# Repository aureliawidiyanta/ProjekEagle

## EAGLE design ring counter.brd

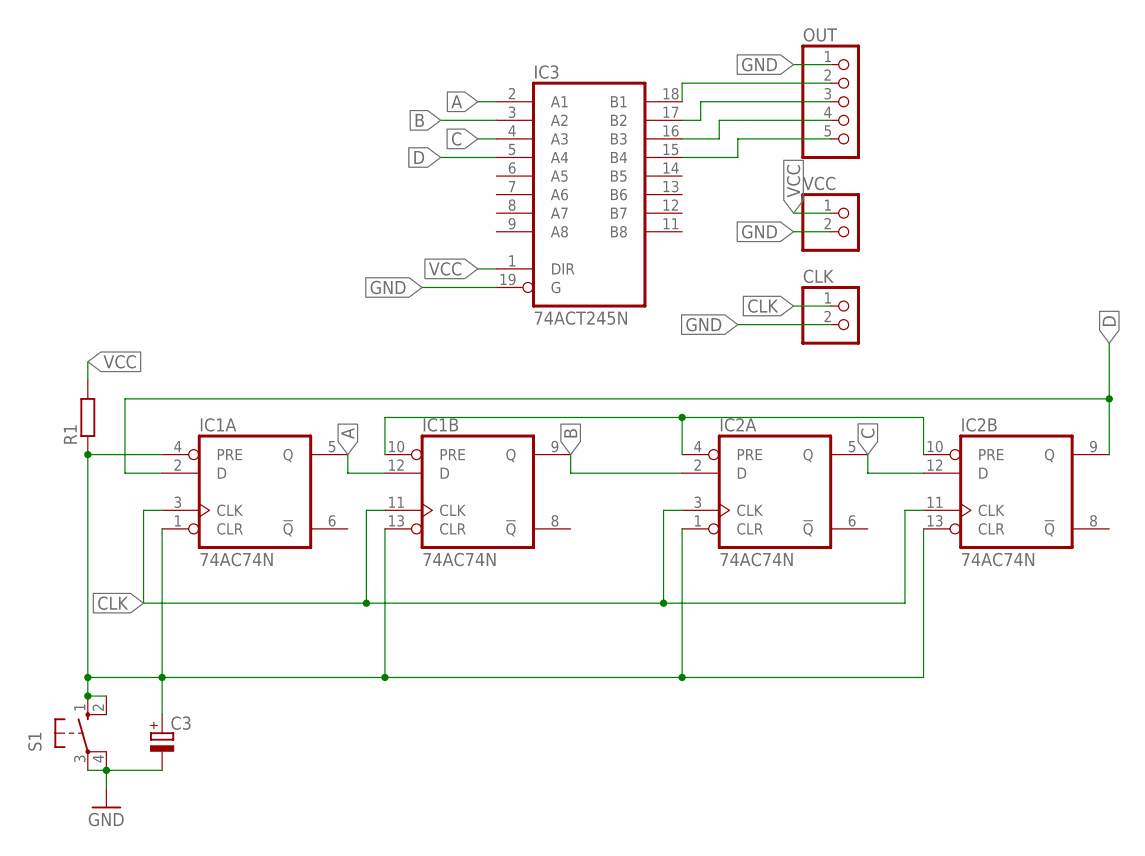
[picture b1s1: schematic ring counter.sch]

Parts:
C3: CPOL-EUE2,5-6E; E2,5-6E
CLK: PINHD-1X2; 1X02
IC1, IC2: 74AC74N; DIL14
IC3: 74ACT245N; DIL20
OUT: PINHD-1X5; 1X05
R1: R-EU_0207/12; 0207/12
S1: 10-XX; B3F-10XX
VCC: PINHD-1X2; 1X02

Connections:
A: IC1.5 (Q), IC1.12 (D), IC3.2 (A1)
B: IC1.9 (Q), IC2.2 (D), IC3.3 (A2)
C: IC2.5 (Q), IC2.12 (D), IC3.4 (A3)
CLK: CLK.1, IC1.3 (CLK), IC1.11 (CLK), IC2.3 (CLK), IC2.11 (CLK)
D: IC1.2 (D), IC2.9 (Q), IC3.5 (A4)
GND: C3.-, CLK.2, IC1.7 (GND), IC2.7 (GND), IC3.10 (GND), IC3.19 (G), OUT.1, S1.3, S1.4 (P1), VCC.2
unnamed: IC1.10 (PRE), IC2.4 (PRE), IC2.10 (PRE)
unnamed: C3.+, IC1.1 (CLR), IC1.4 (PRE), IC1.13 (CLR), IC2.1 (CLR), IC2.13 (CLR), R1.1, S1.1 (S), S1.2 (S1)
unnamed: IC3.18 (B1), OUT.2
unnamed: IC3.17 (B2), OUT.3
unnamed: IC3.16 (B3), OUT.4
unnamed: IC3.15 (B4), OUT.5
VCC: IC1.14 (VCC), IC2.14 (VCC), IC3.1 (DIR), IC3.20 (VCC), R1.2, VCC.1

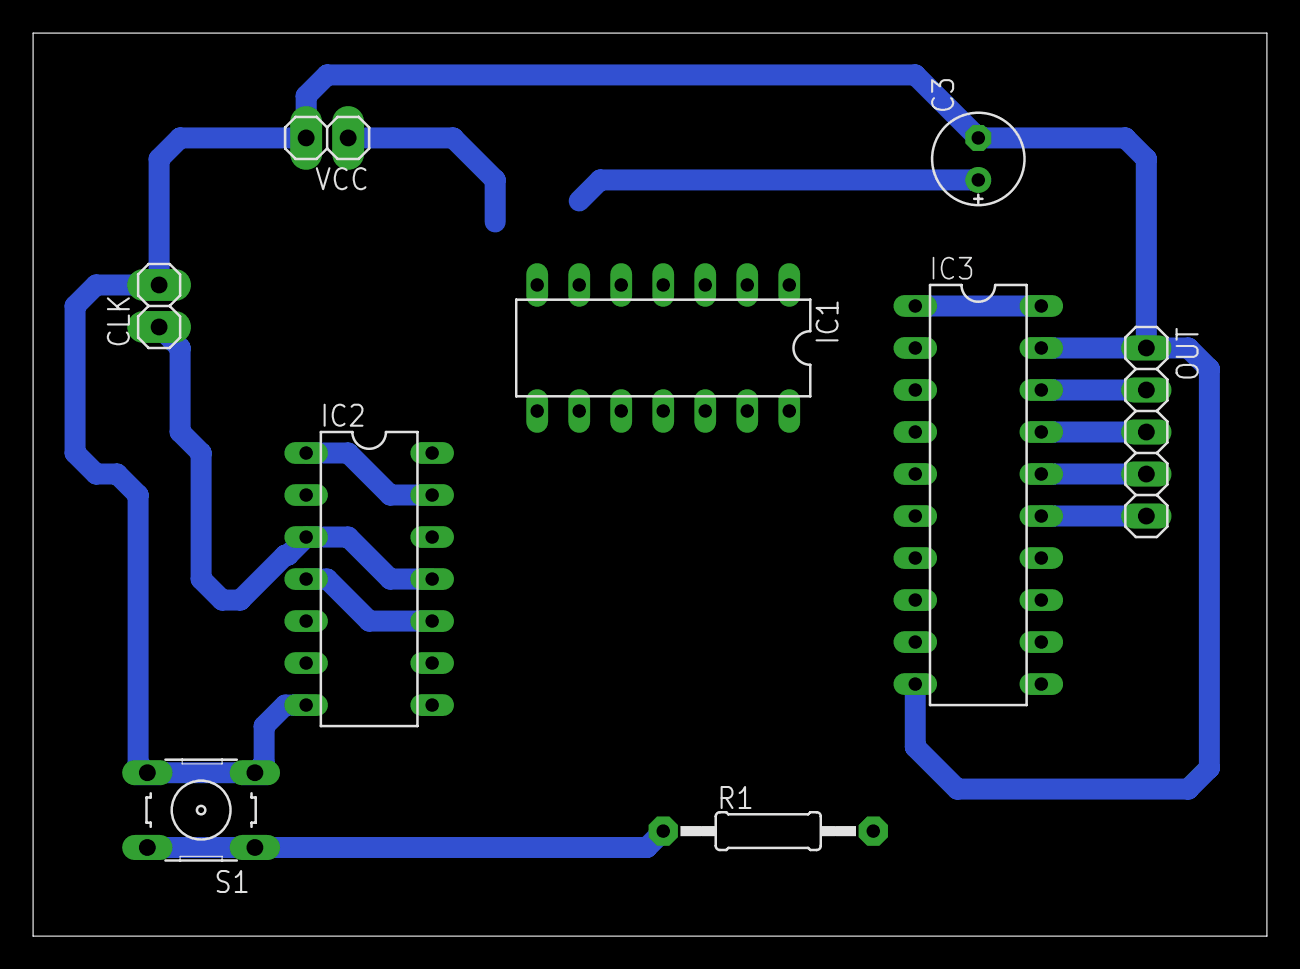
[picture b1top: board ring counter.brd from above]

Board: 2 copper layers, 74.6 x 54.6 mm, 9 parts (0 on the bottom side), 13 nets.

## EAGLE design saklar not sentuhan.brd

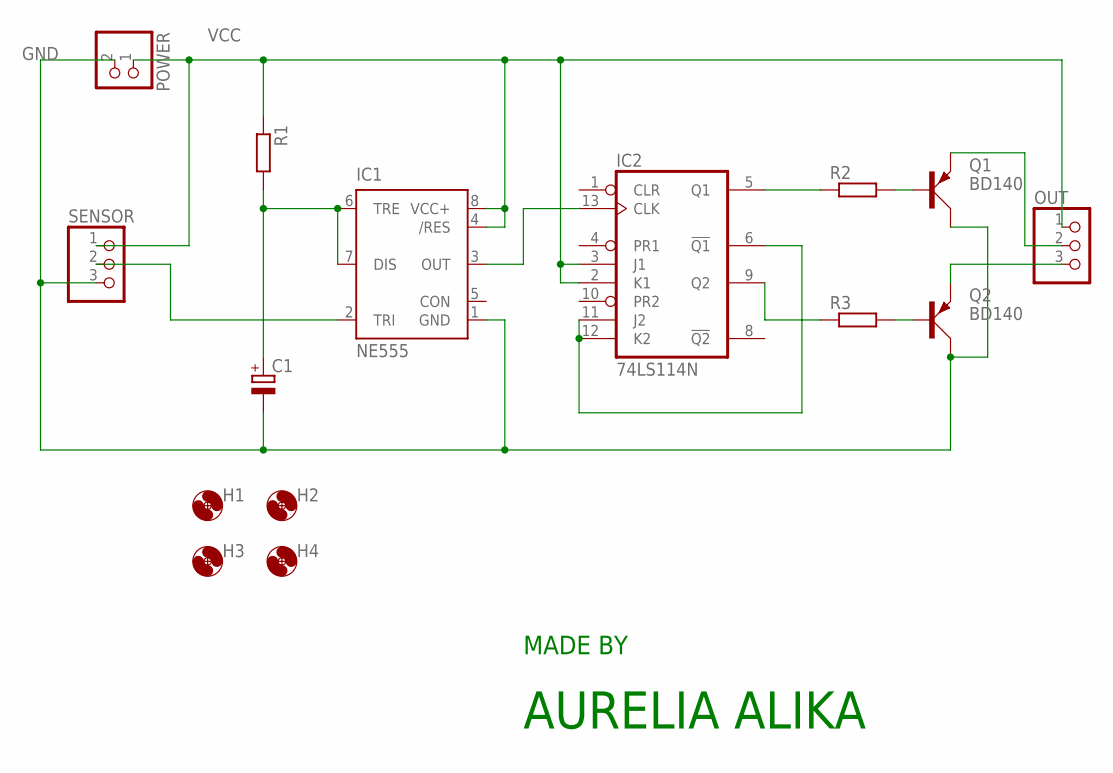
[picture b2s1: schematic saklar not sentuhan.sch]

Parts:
C1: CPOL-EUE2,5-6E; E2,5-6E
H1, H2, H3, H4: MOUNT-HOLE3.6; 3,6
IC1: NE555; DIL-08
IC2: 74LS114N; DIL14
OUT: PINHD-1X3; 1X03
POWER: PINHD-1X2; 1X02
Q1, Q2: BD140; TO126AV
R1, R2, R3: R-EU_0207/15; 0207/15
SENSOR: PINHD-1X3; 1X03

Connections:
GND: C1.-, IC1.1 (GND), IC2.7 (GND), POWER.2, Q1.C, Q2.C, SENSOR.3
unnamed: IC1.3 (OUT), IC2.13 (CLK)
unnamed: OUT.2, Q1.E
unnamed: IC2.5 (Q1), R2.1
unnamed: OUT.3, Q2.E
unnamed: C1.+, IC1.6 (TRE), IC1.7 (DIS), R1.2
unnamed: IC1.2 (TRI), SENSOR.2
unnamed: Q1.B, R2.2
unnamed: IC2.9 (Q2), R3.1
unnamed: Q2.B, R3.2
unnamed: IC2.6 (!Q1), IC2.11 (J2), IC2.12 (K2)
VCC: IC1.4 (/RES), IC1.8 (VCC+), IC2.2 (K1), IC2.3 (J1), IC2.14 (VCC), OUT.1, POWER.1, R1.1, SENSOR.1

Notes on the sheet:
MADE BY
AURELIA ALIKA

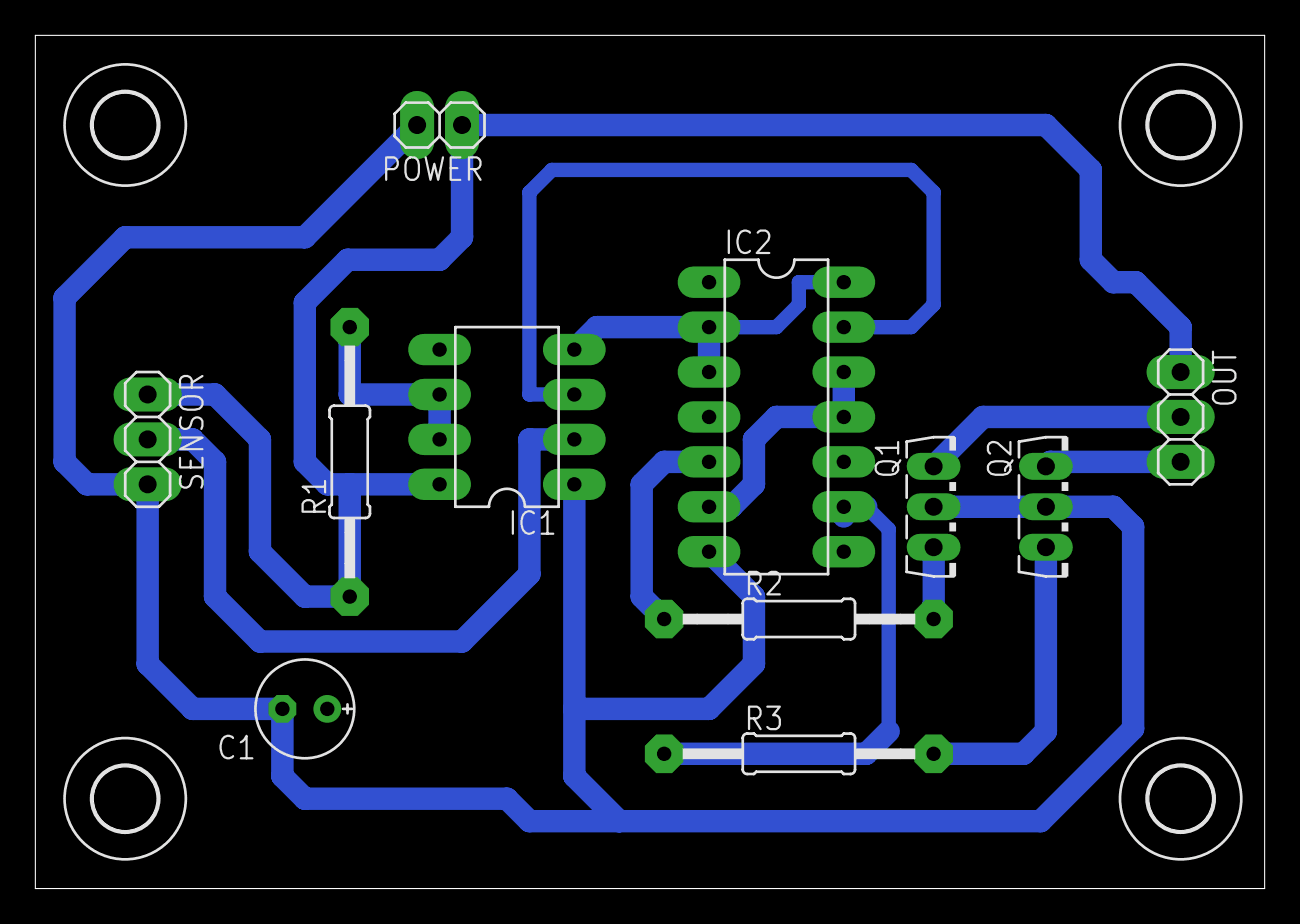
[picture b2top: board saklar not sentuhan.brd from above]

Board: 2 copper layers, 69.5 x 48.2 mm, 15 parts (0 on the bottom side), 12 nets.

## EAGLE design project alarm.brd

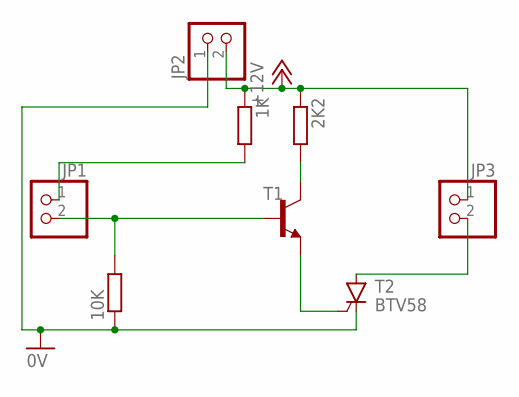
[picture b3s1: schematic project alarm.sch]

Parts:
1K, 2K2, 10K: R-EU_0207/15; 0207/15
JP1, JP2, JP3: PINHD-1X2; 1X02
T1: BC107A-NPN-TO18-EBC; TO18
T2: BTV58; TO220CS

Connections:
0V: 10K.1, JP2.1, T2.C
+12V: 1K.1, 2K2.1, JP2.2, JP3.1
unnamed: 10K.2, JP1.2, T1.2 (B)
unnamed: 2K2.2, T1.3 (C)
unnamed: 1K.2, JP1.1
unnamed: T1.1 (E), T2.G
unnamed: JP3.2, T2.A

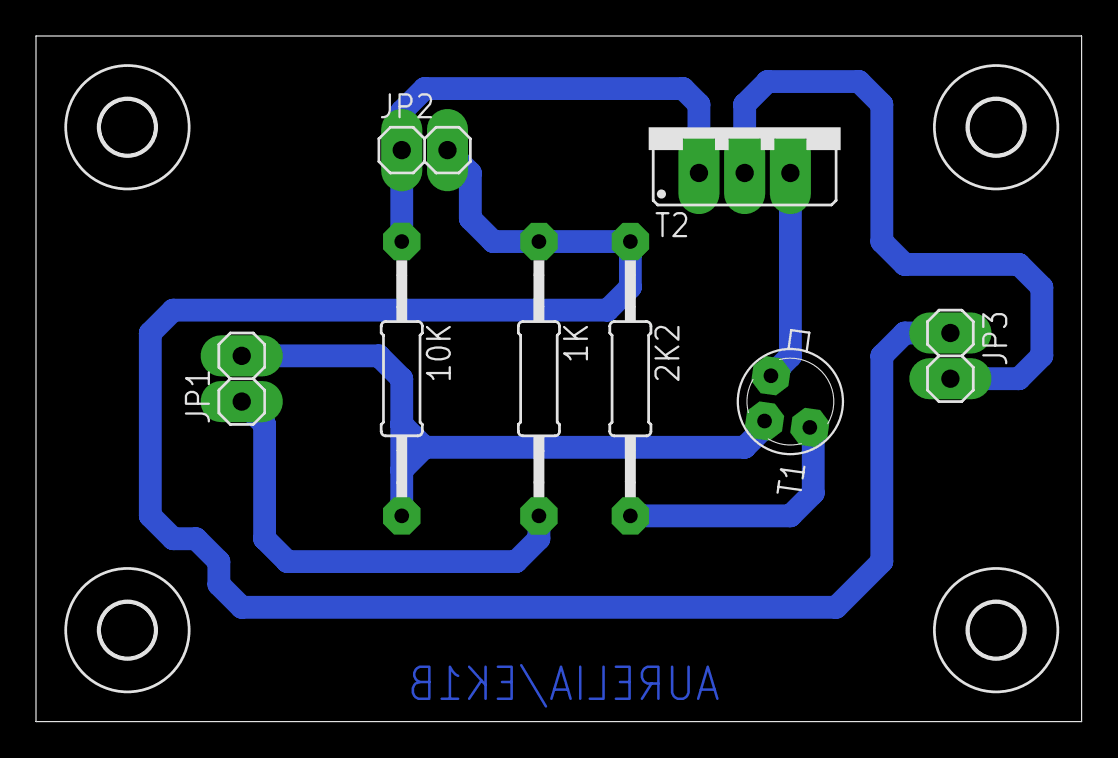
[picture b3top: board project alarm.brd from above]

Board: 2 copper layers, 58.1 x 38.1 mm, 12 parts (0 on the bottom side), 7 nets.

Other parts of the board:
U$1, U$2, U$3, U$4: 3,0

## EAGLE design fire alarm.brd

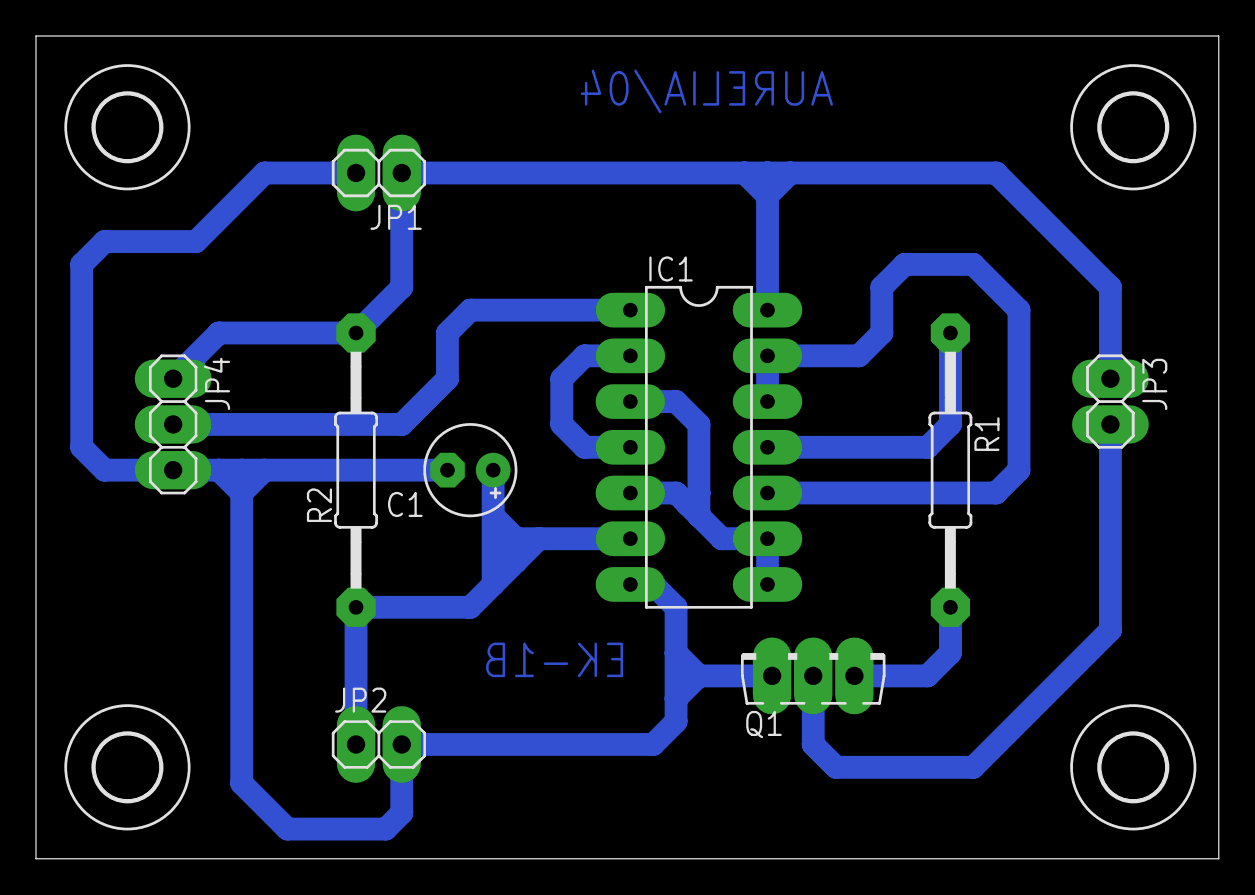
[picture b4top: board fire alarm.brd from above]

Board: 2 copper layers, 65.7 x 45.7 mm, 13 parts (0 on the bottom side), 10 nets.

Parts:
C1: E2,5-5
H1, H2, H3, H4: MOUNT-HOLE3.6; 3,6
IC1: 4093N; DIL14
JP1, JP2, JP3: 1X02
JP4: 1X03
Q1: BD139; TO126AV
R1, R2: 0207/15

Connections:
unnamed: IC1.11, R1.1
unnamed: IC1.2, IC1.4
unnamed: IC1.3, IC1.5, IC1.8, IC1.9
unnamed: Q1.B, R1.2
unnamed: IC1.10, IC1.12, IC1.13
unnamed: C1.+, IC1.6, JP2.1, R2.1
unnamed: IC1.1, JP4.2
unnamed: JP3.2, Q1.C
VDD: IC1.14, JP1.1, JP3.1, JP4.1, R2.2
VSS: C1.-, IC1.7, JP1.2, JP2.2, JP4.3, Q1.E

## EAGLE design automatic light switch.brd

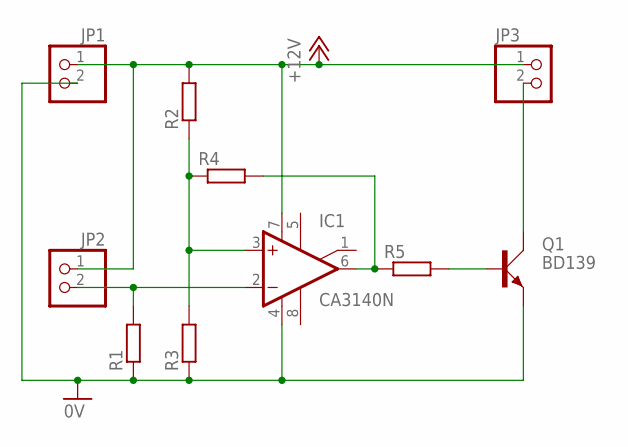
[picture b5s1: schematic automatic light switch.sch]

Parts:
IC1: CA3140N; DIL08
JP1, JP2, JP3: PINHD-1X2; 1X02
Q1: BD139; TO126AV
R1, R2, R3, R4, R5: R-EU_0207/15; 0207/15

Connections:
0V: IC1.4 (V-), JP1.2, Q1.E, R1.1, R3.1
+12V: IC1.7 (V+), JP1.1, JP2.1, JP3.1, R2.2
unnamed: IC1.2 (-IN), JP2.2, R1.2
unnamed: IC1.3 (+IN), R2.1, R3.2, R4.1
unnamed: IC1.6 (OUT), R4.2, R5.1
unnamed: Q1.B, R5.2
unnamed: JP3.2, Q1.C

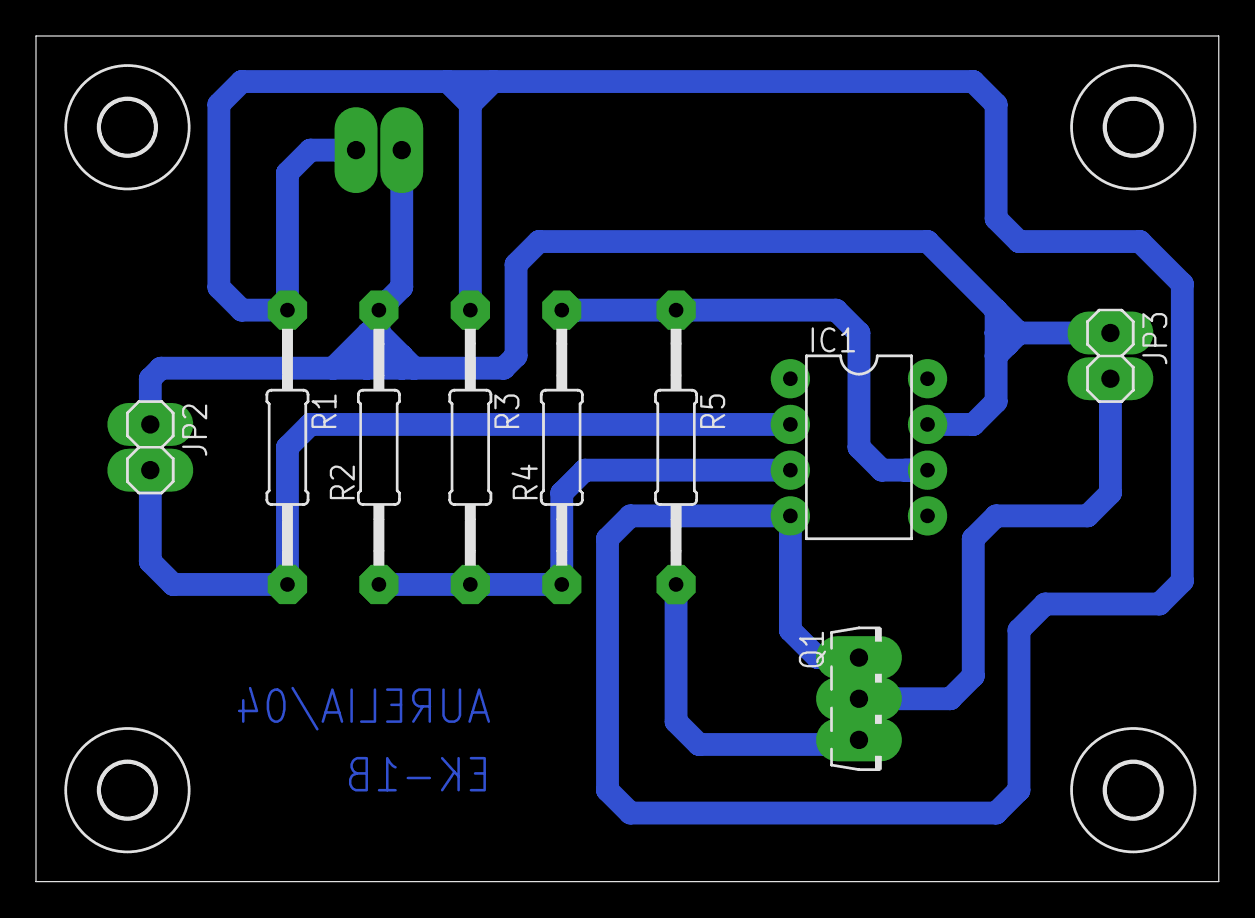
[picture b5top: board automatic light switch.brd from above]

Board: 2 copper layers, 65.7 x 47.0 mm, 14 parts (1 on the bottom side), 7 nets.

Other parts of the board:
U$1, U$2, U$3, U$4: 3,0

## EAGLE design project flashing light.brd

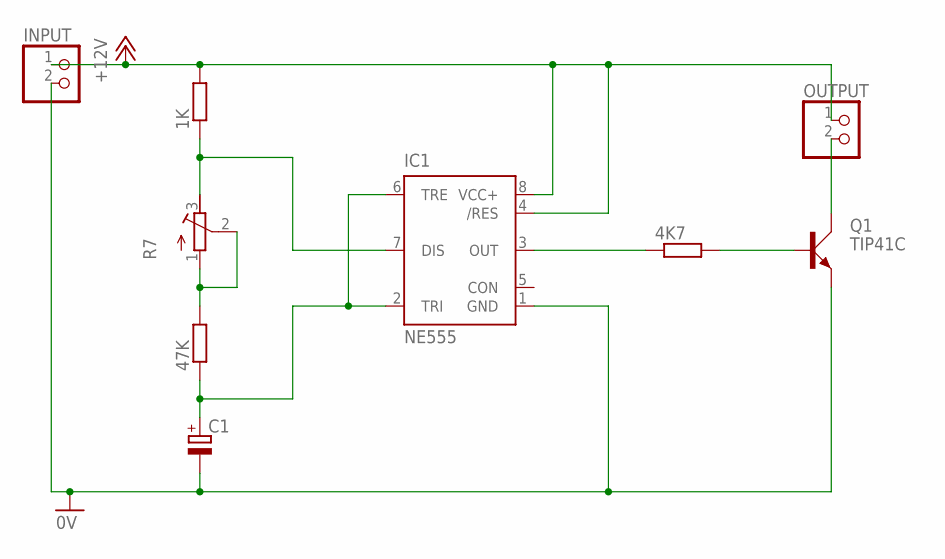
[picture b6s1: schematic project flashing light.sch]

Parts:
1K, 4K7, 47K: R-EU_0207/15; 0207/15
C1: CPOL-EUE2.5-6; E2,5-6
IC1: NE555; DIL-08
INPUT: PINHD-1X2; 1X02
OUTPUT: PINHD-1X2; 1X02
Q1: TIP41C; TO220AV
R7: R-TRIMM3339P; RTRIM3339P

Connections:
0V: C1.-, IC1.1 (GND), INPUT.2, Q1.E
+12V: 1K.2, IC1.4 (/RES), IC1.8 (VCC+), INPUT.1, OUTPUT.1
unnamed: 47K.1, C1.+, IC1.2 (TRI), IC1.6 (TRE)
unnamed: OUTPUT.2, Q1.C
unnamed: 47K.2, R7.1 (A), R7.2 (S)
unnamed: 1K.1, IC1.7 (DIS), R7.3 (E)
unnamed: 4K7.1, IC1.3 (OUT)
unnamed: 4K7.2, Q1.B

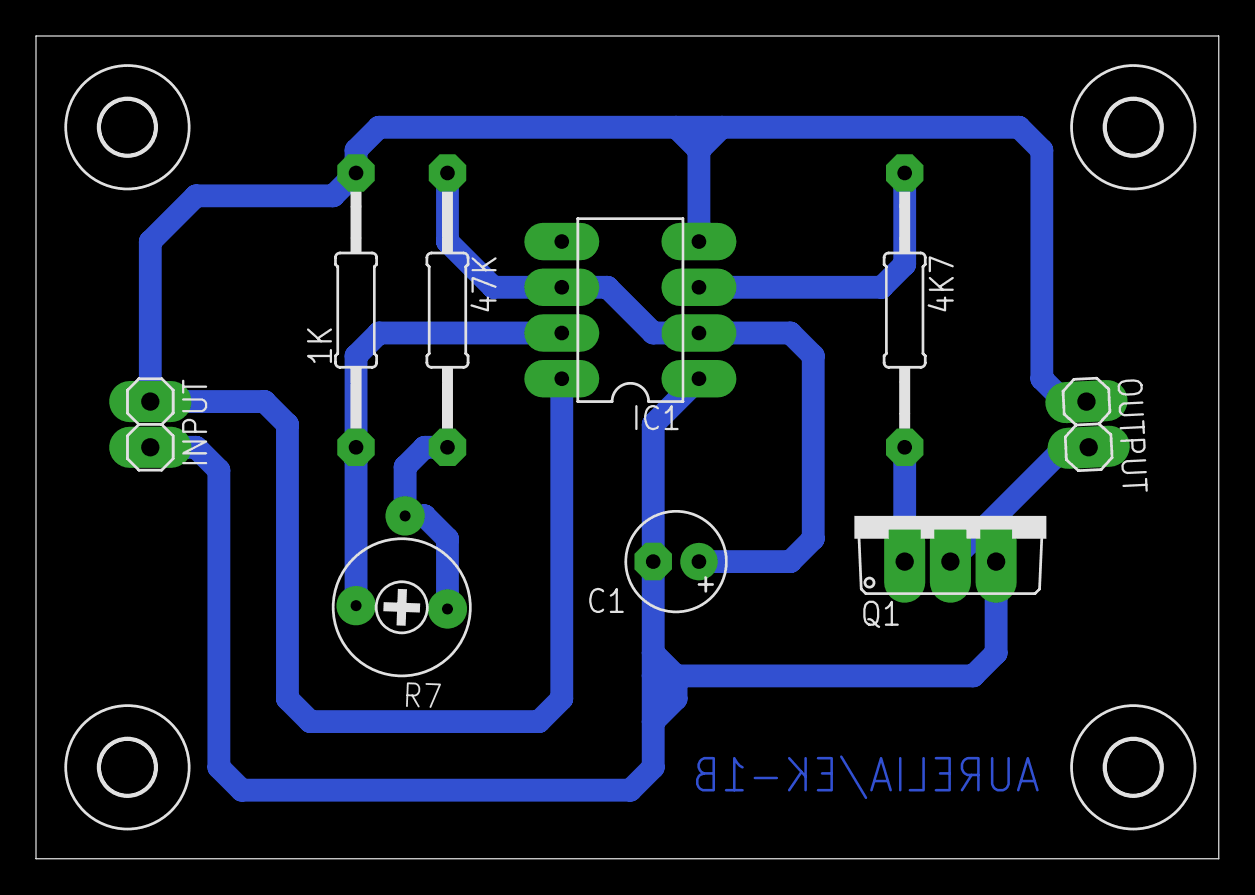
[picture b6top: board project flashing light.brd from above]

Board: 2 copper layers, 65.7 x 45.7 mm, 13 parts (0 on the bottom side), 8 nets.

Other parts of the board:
U$1, U$2, U$3, U$4: 3,0

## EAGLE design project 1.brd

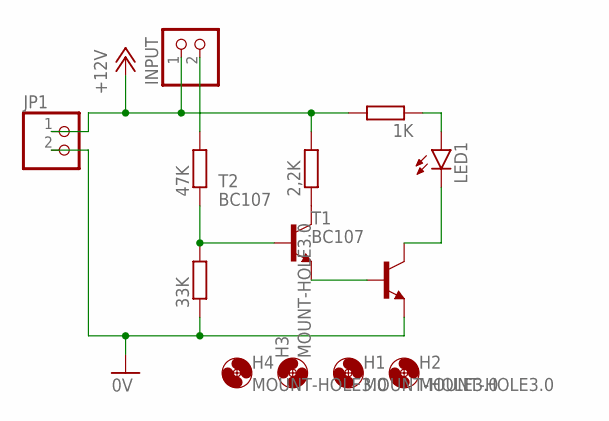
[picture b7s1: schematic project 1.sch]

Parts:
1K: R-EU_0207/12; 0207/12
2,2K, 33K, 47K: R-EU_0207/15; 0207/15
H1, H2, H3, H4: MOUNT-HOLE3.0; 3,0
INPUT: PINHD-1X2; 1X02
JP1: PINHD-1X2; 1X02
LED1: LED5MM
T1, T2: BC107; TO18

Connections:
0V: 33K.1, JP1.2, T1.1 (E)
+12V: 1K.2, 2,2K.2, INPUT.1, JP1.1
unnamed: 47K.2, INPUT.2
unnamed: 33K.2, 47K.1, T2.2 (B)
unnamed: 2,2K.1, T2.3 (C)
unnamed: T1.2 (B), T2.1 (E)
unnamed: LED1.K (C), T1.3 (C)
unnamed: 1K.1, LED1.A

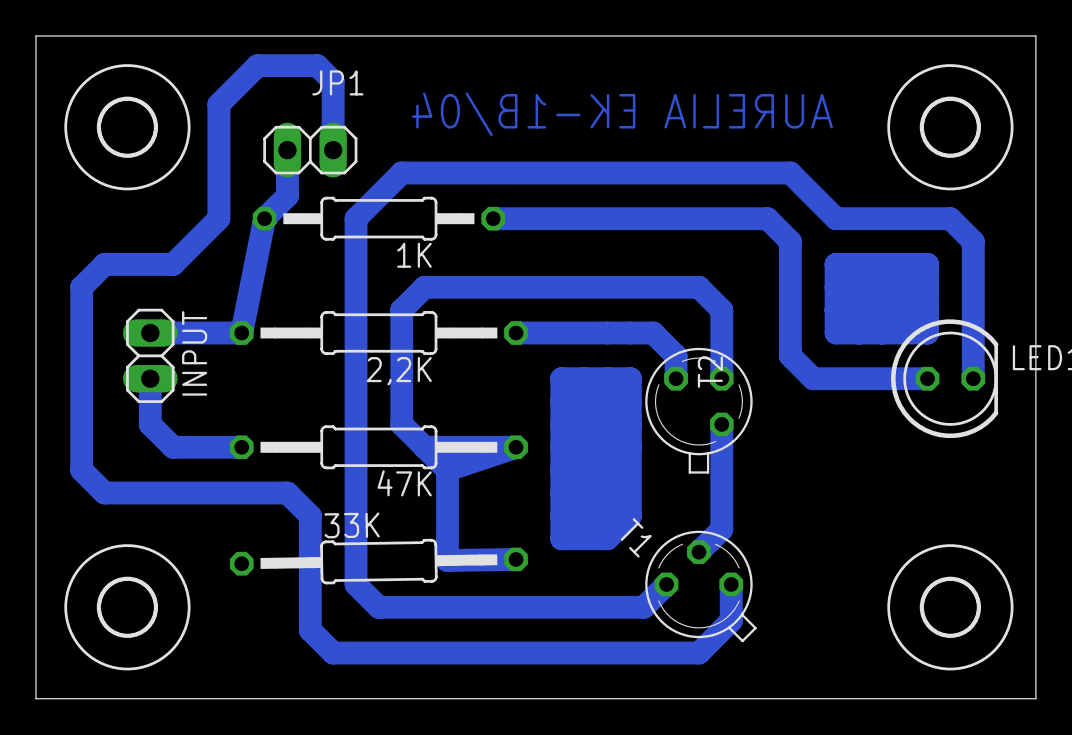
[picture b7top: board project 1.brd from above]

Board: 2 copper layers, 55.5 x 36.8 mm, 13 parts (0 on the bottom side), 8 nets.

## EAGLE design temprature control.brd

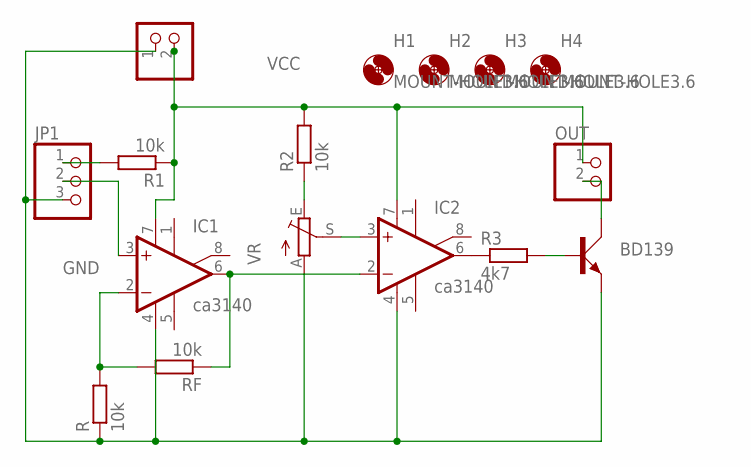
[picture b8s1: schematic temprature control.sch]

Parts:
H1, H2, H3, H4: MOUNT-HOLE3.6; 3,6
IC1, IC2: ca3140; DIL08
JP1: PINHD-1X3; 1X03
OUT: PINHD-1X2; 1X02
Q1: BD139; TO126AV
R, R1, R2: 10k; 0207/15
R3: 4k7; 0207/15
RF: 10k; 0207/15
VCC: PINHD-1X2; 1X02
VR: TRIM_EU-LI10; LI10

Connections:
GND: IC1.4 (V-), IC2.4 (V-), JP1.3, Q1.E, R.1, VCC.1, VR.A
unnamed: Q1.B, R3.2
unnamed: IC1.3 (+IN), JP1.2
unnamed: OUT.2, Q1.C
unnamed: JP1.1, R1.2
unnamed: IC1.2 (-IN), R.2, RF.2
unnamed: IC1.6 (OUT), IC2.2 (-IN), RF.1
unnamed: IC2.6 (OUT), R3.1
unnamed: R2.1, VR.E
unnamed: IC2.3 (+IN), VR.S
VCC: IC1.7 (V+), IC2.7 (V+), OUT.1, R1.1, R2.2, VCC.2

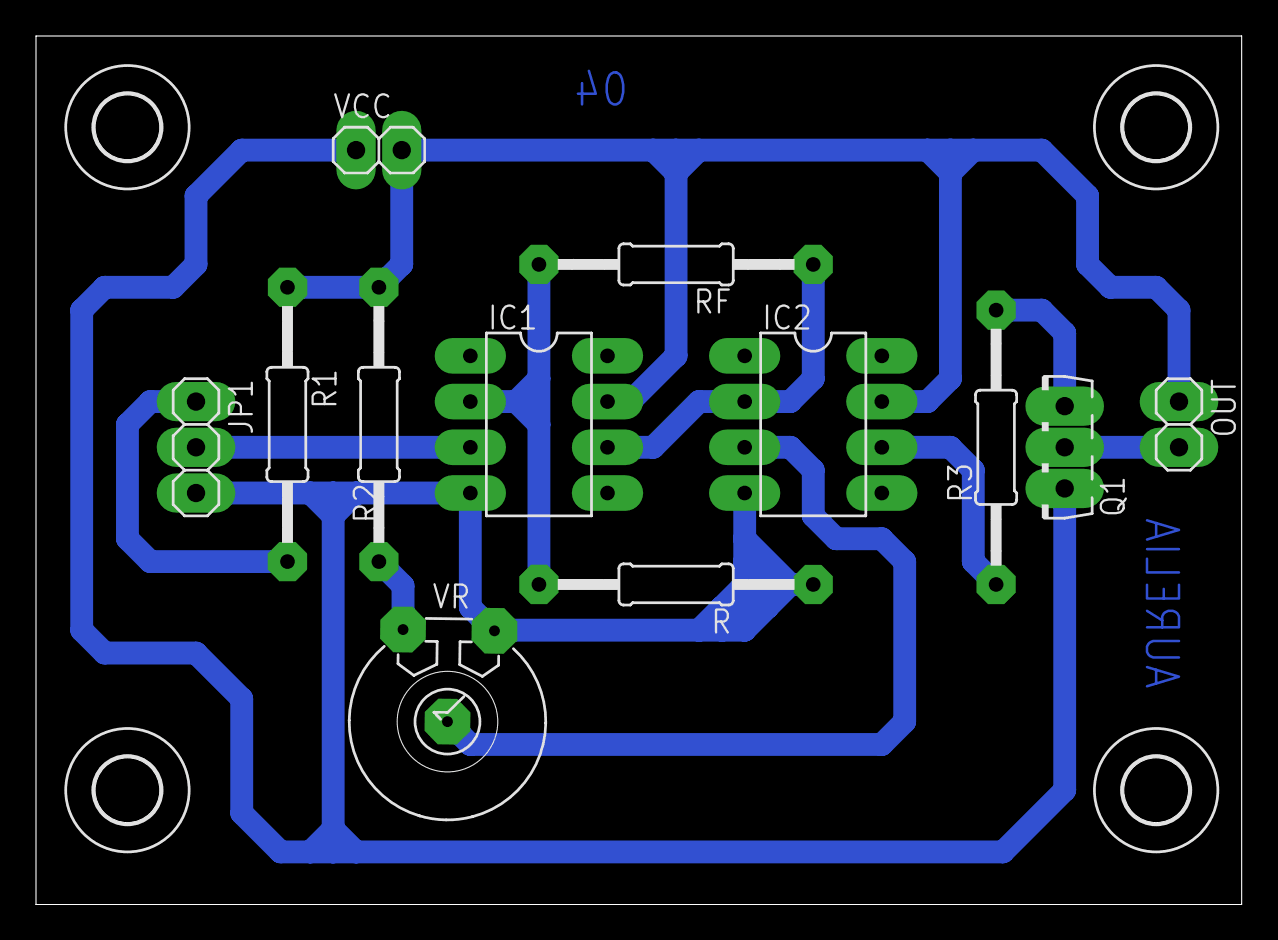
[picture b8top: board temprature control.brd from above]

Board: 2 copper layers, 67.0 x 48.2 mm, 16 parts (0 on the bottom side), 11 nets.
